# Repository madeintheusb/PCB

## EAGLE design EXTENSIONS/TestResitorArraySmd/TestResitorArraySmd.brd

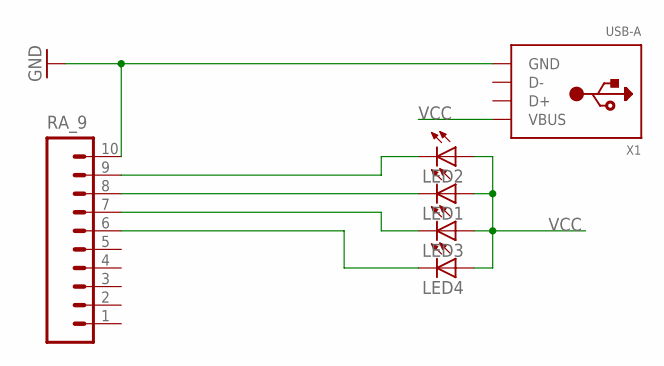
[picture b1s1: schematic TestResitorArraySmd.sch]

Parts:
LED1, LED2, LED3, LED4: LEDSMT1206; 1206
RA_9: M10SMD_MALE; 1X10_SMD_MALE
X1: USB-A; MOLEX_480371000

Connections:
GND: RA_9.10, X1.4 (GND)
unnamed: LED2.C, RA_9.9
unnamed: LED1.C, RA_9.8
unnamed: LED3.C, RA_9.7
unnamed: LED4.C, RA_9.6
VCC: LED1.A, LED2.A, LED3.A, LED4.A, X1.1 (VBUS)

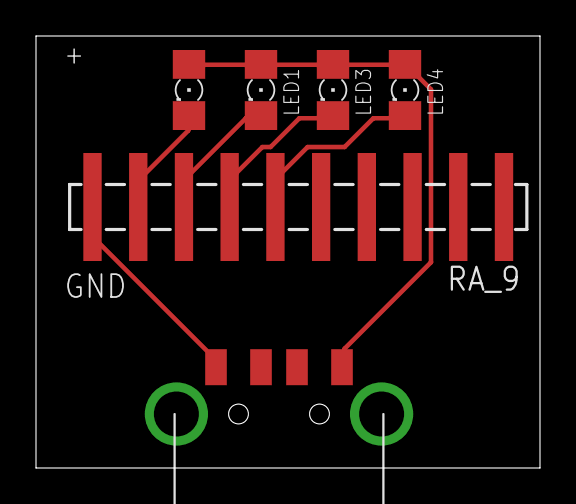
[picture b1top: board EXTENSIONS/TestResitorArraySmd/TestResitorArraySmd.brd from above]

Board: 2 copper layers, 28.0 x 24.0 mm, 6 parts (0 on the bottom side), 6 nets.

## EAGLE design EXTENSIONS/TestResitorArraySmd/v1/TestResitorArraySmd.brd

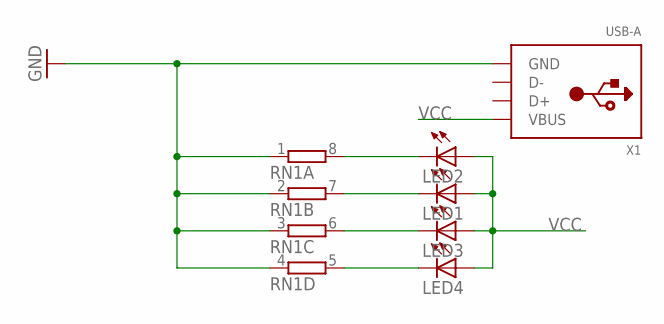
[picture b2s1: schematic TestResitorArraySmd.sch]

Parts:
LED1, LED2, LED3, LED4: LEDSMT1206; 1206
RN1: 4R-NCAT16; CAT16
X1: USB-A; MOLEX_480371000

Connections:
GND: RN1.1, RN1.2 (1), RN1.3 (1), RN1.4 (1), X1.4 (GND)
unnamed: LED2.C, RN1.8 (2)
unnamed: LED1.C, RN1.7 (2)
unnamed: LED3.C, RN1.6 (2)
unnamed: LED4.C, RN1.5 (2)
VCC: LED1.A, LED2.A, LED3.A, LED4.A, X1.1 (VBUS)

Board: 2 copper layers, 6 parts (0 on the bottom side), 6 nets, no tracks yet.

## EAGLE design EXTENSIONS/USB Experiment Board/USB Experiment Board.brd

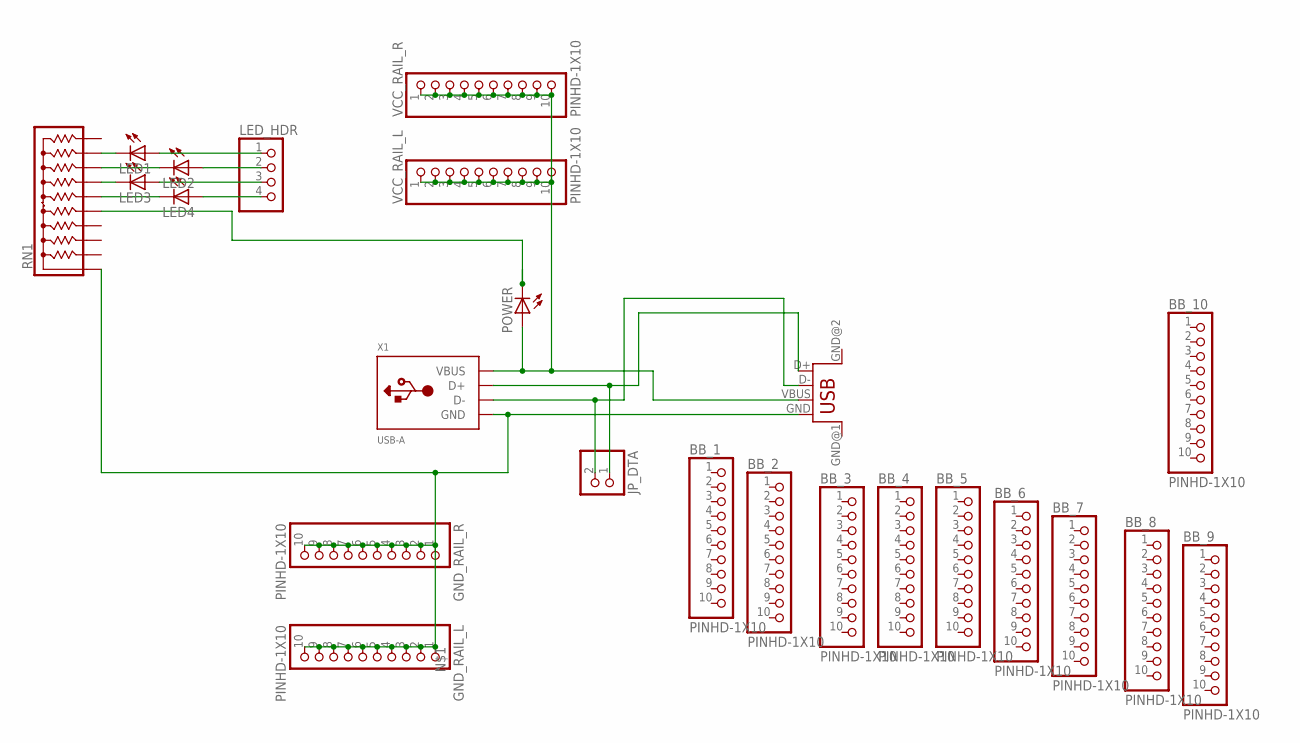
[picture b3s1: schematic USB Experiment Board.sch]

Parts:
BB_1, BB_2, BB_3, BB_4, BB_5, BB_6, BB_7, BB_8, BB_9, BB_10: PINHD-1X10; 1X10-BIG
GND_RAIL_L: PINHD-1X10; 1X10-BIG
GND_RAIL_R: PINHD-1X10; 1X10-BIG
JP_DTA: PINHD-1X2; 1X02
LED1, LED2, LED3, LED4: LEDSMT1206; 1206
LED_HDR: PINHD-1X4; 1X04
POWER: LEDSMT1206; 1206
RN1: 4610X; SIP10
U$1: USB; USB-FEMALE-A-PTH
VCC_RAIL_L: PINHD-1X10; 1X10-BIG
VCC_RAIL_R: PINHD-1X10; 1X10-BIG
X1: USB-A; MOLEX_480371000

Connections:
unnamed: GND_RAIL_L.1, GND_RAIL_L.2, GND_RAIL_L.3, GND_RAIL_L.4, GND_RAIL_L.5, GND_RAIL_L.6, GND_RAIL_L.7, GND_RAIL_L.8, GND_RAIL_L.9, GND_RAIL_L.10, GND_RAIL_R.1, GND_RAIL_R.2, GND_RAIL_R.3, GND_RAIL_R.4, GND_RAIL_R.5, GND_RAIL_R.6, GND_RAIL_R.7, GND_RAIL_R.8, GND_RAIL_R.9, GND_RAIL_R.10, RN1.1, U$1.GND, X1.4 (GND)
unnamed: LED1.C, RN1.9
unnamed: JP_DTA.1, U$1.D+, X1.3 (D+)
unnamed: JP_DTA.2, U$1.D-, X1.2 (D-)
unnamed: LED2.C, RN1.8
unnamed: LED3.C, RN1.7
unnamed: LED4.C, RN1.6
unnamed: LED1.A, LED_HDR.1
unnamed: LED2.A, LED_HDR.2
unnamed: LED3.A, LED_HDR.3
unnamed: LED4.A, LED_HDR.4
unnamed: POWER.C, RN1.5
VCC: POWER.A, U$1.VBUS, VCC_RAIL_L.1, VCC_RAIL_L.2, VCC_RAIL_L.3, VCC_RAIL_L.4, VCC_RAIL_L.5, VCC_RAIL_L.6, VCC_RAIL_L.7, VCC_RAIL_L.8, VCC_RAIL_L.9, VCC_RAIL_L.10, VCC_RAIL_R.1, VCC_RAIL_R.2, VCC_RAIL_R.3, VCC_RAIL_R.4, VCC_RAIL_R.5, VCC_RAIL_R.6, VCC_RAIL_R.7, VCC_RAIL_R.8, VCC_RAIL_R.9, VCC_RAIL_R.10, X1.1 (VBUS)

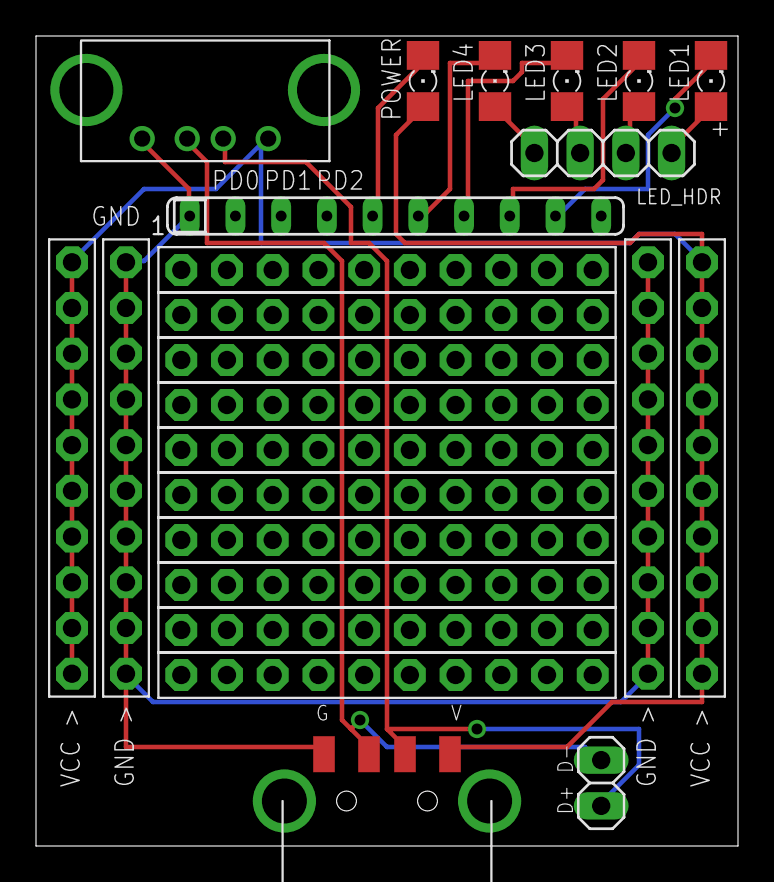
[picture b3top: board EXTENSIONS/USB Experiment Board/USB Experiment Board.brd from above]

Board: 2 copper layers, 39.0 x 45.0 mm, 24 parts (0 on the bottom side), 13 nets.

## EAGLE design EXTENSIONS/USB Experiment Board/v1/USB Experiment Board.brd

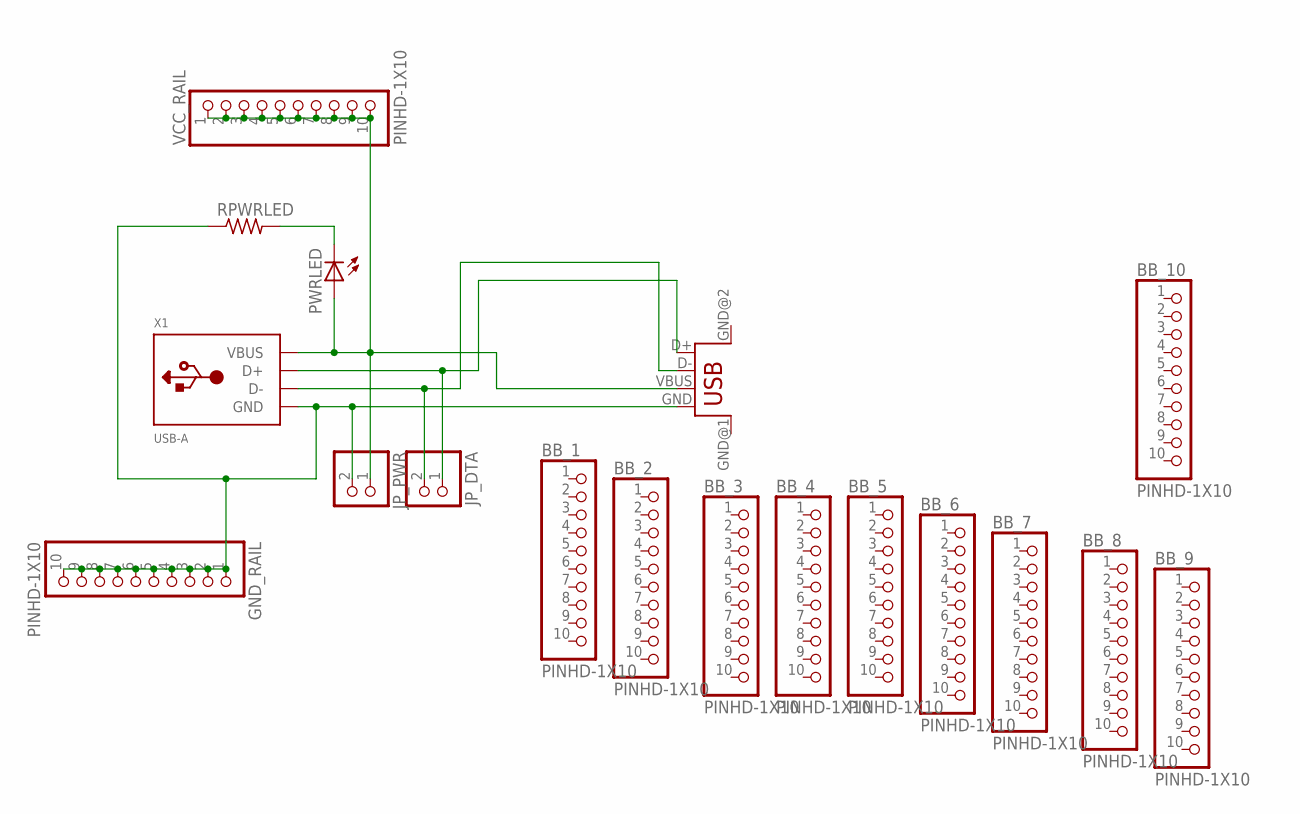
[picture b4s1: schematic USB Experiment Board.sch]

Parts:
BB_1, BB_2, BB_3, BB_4, BB_5, BB_6, BB_7, BB_8, BB_9, BB_10: PINHD-1X10; 1X10-BIG
GND_RAIL: PINHD-1X10; 1X10-BIG
JP_DTA: PINHD-1X2; 1X02
JP_PWR: PINHD-1X2; 1X02
PWRLED: LEDCHIPLED_0805; CHIPLED_0805
RPWRLED: R-US_R0805; R0805
U$1: USB; USB-FEMALE-A-PTH
VCC_RAIL: PINHD-1X10; 1X10-BIG
X1: USB-A; MOLEX_480371000

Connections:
unnamed: GND_RAIL.1, GND_RAIL.2, GND_RAIL.3, GND_RAIL.4, GND_RAIL.5, GND_RAIL.6, GND_RAIL.7, GND_RAIL.8, GND_RAIL.9, GND_RAIL.10, JP_PWR.2, RPWRLED.1, U$1.GND, X1.4 (GND)
unnamed: JP_DTA.1, U$1.D+, X1.3 (D+)
unnamed: JP_DTA.2, U$1.D-, X1.2 (D-)
unnamed: JP_PWR.1, PWRLED.A, U$1.VBUS, VCC_RAIL.1, VCC_RAIL.2, VCC_RAIL.3, VCC_RAIL.4, VCC_RAIL.5, VCC_RAIL.6, VCC_RAIL.7, VCC_RAIL.8, VCC_RAIL.9, VCC_RAIL.10, X1.1 (VBUS)
unnamed: PWRLED.C, RPWRLED.2

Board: 2 copper layers, 18 parts (0 on the bottom side), 5 nets, no tracks yet.

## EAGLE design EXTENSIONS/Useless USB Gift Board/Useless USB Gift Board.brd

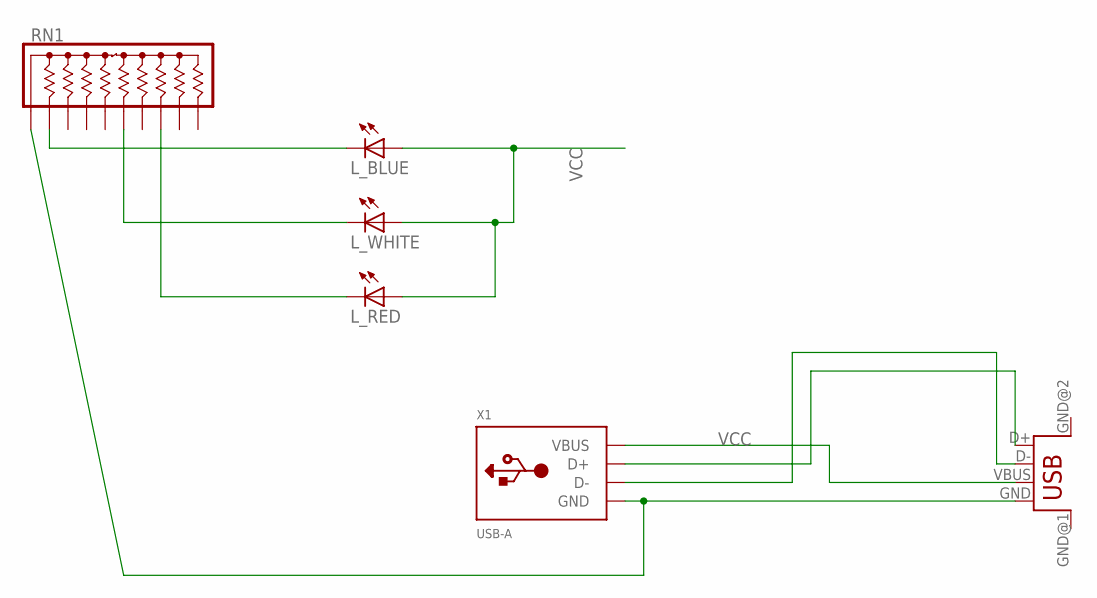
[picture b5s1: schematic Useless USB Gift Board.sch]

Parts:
L_BLUE: LED5MM
L_RED: LED5MM
L_WHITE: LED5MM
RN1: 4610X; SIP10
U$1: USB; USB-FEMALE-A-PTH
X1: USB-A; MOLEX_480371000

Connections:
unnamed: RN1.1, U$1.GND, X1.4 (GND)
unnamed: L_BLUE.K (C), RN1.2
unnamed: U$1.D+, X1.3 (D+)
unnamed: U$1.D-, X1.2 (D-)
unnamed: L_RED.K (C), RN1.8
unnamed: L_WHITE.K (C), RN1.6
VCC: L_BLUE.A, L_RED.A, L_WHITE.A, U$1.VBUS, X1.1 (VBUS)

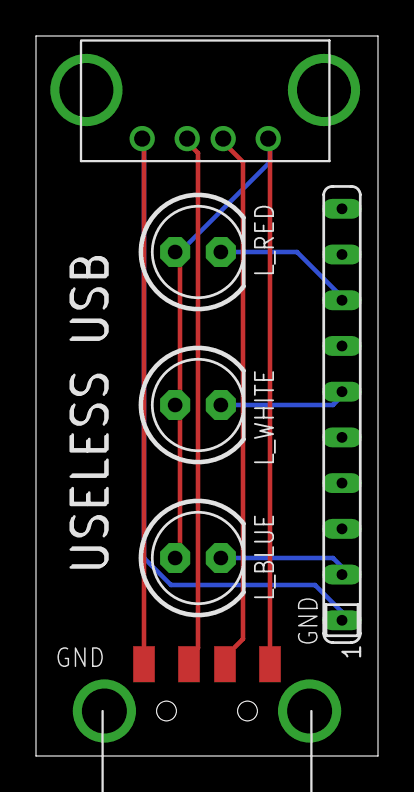
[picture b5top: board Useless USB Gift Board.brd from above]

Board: 2 copper layers, 19.0 x 40.0 mm, 6 parts (0 on the bottom side), 7 nets.

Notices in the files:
parts and their libraries:
SparkFun-Connectors: Licensing: Creative Commons ShareAlike 4.0 International - https://creativecommons.org/licenses/by-sa/4.0
